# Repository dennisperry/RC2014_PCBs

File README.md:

# PCBs for RC2014
I started with a simple RC2014 Classic II as something interesting to try a new logic analyze. Then built a Zeta2 to get more capability; CP/M etal using ROMWBW. However; the Zeta2 didn't allow for much hardware expansion so I returned to the RC2014 and was confronted with its low cost simplicity. The Classic II is optimized for cost not unfettered expansion. Instead I've redone all the PCBs for the RC2014 with operational independence in mind. No more one clock per system to drive CPU and UART. What I've arrived at is something close to a Zeta2 in RC2014 form factor.

I've used SMT on pretty much all the boards. In my professional life I've done a lot of work with SMT and don't find it that difficult. I'd recommend some solder paste and a hot air setup along with a good soldering iron, a flux pen and various sizes of solder wick. I've converted a toaster oven into a reflow oven for when I'm doing more that one unit builds. This route requires you purchase a solder paste stencil with your PCBs.

No attempt is made to make the boards the same size or particularly pretty, these boards were started with the tariffs at their peak and every sq inch was expensive. The routing is from the FreeRouting plug-in to KiCad. Some of the rough edges are fixed but I didn't want to make them a lifetime project.

If you are a small club or other organization you could get the boards built by someone like JLCPCB or the likes and not have to deal with the SMT issue.

What's missing; generally there is no complete BOM. A BOM can be generated from the KiCad schematic along with looking at the package type. My general practice was to build up a list on Digikey or Mouser as I designed the board. Also combined with what stock I have on hand along with contributions from ebay, Amazon and JameCo.

# 64K RAM/ROM Battery Backed Memory Board for RC2014
One of the last boards I built is a 64k ROM/RAM board without banking. I needed something simpler for a project than the Zeta2 banking system. It is not efficient with memory usage but flexible in being able to make many different memory maps. The ROM can be manually bank selected and will accept any of the SST39SF0x0 flash ICs. The jumpers allow RAM or ROM to traded in 4K block across the memory map. The RAM is battery backed. I use a non-banked version of SCM on this board. If you change your ROM frequently experimenting you will appreciate the 32 pin ZIF socket (look on Amazon for the ZIF).

# Backplane with UART for RC2014

This backplane is built with a 16550 UART which will save 1 slot and pretty much every system will need a basic serial port. The UART is supplied with its own oscillator to make it independent of the other parts of the system.

# Z80 CPU for RC2014
A simple card with its own oscillator which can be either the 8 or 14 pin sizes. Clock can be put on the bus or not by jumper.

# 512K RAM/ROM MEMORY for RC2014
This is a Zeta2 compatible bank select memory board. Allows full ROMWBW CP/M system with ROM and RAM disks. Again experimenters will appreciate the 32 pin ZIF socket. It does lack the battery backup of the Zeta2 so your ROMWBW RAM disk will not survive power cycles.

# 16550 UART for RC2014
Done before the backplane with UART, is Zeta2 compatible using ROMWBW. Has its own clock, and has pinout for a standard FTDI TTL to USB UART adapter.

# Z80 CTC DS1302 RTC for RC2014
This board is Zeta2 compatible with ROMWBW. The RTC is battery backed. Generates periodic interrupts using tpye 2 interrupts.

# PPIDE for RC2014
Again Zeta2 compatible with ROMWBW. Supports power for a CF Card adapter. I use this with a CF card adapter combined with a CF to SD card adapter. You can load all the ROMWBW disk images on a reasonable SD card.

# FDC for RC2014
Zeta2 compatible with ROMWBW. I found that once I had the PPIDE board in my system I really had no need for the FDC but it works fine.

# 8 BIT ARDUINO PRO MICRO INTERFACE for RC2014
Uses the Arduino Pro Micro with a ATmega32U4 with built in USB. WARNING this board has been barely smoke tested. I made it to potentially use it as a UART replacement but have not gotten around to it.

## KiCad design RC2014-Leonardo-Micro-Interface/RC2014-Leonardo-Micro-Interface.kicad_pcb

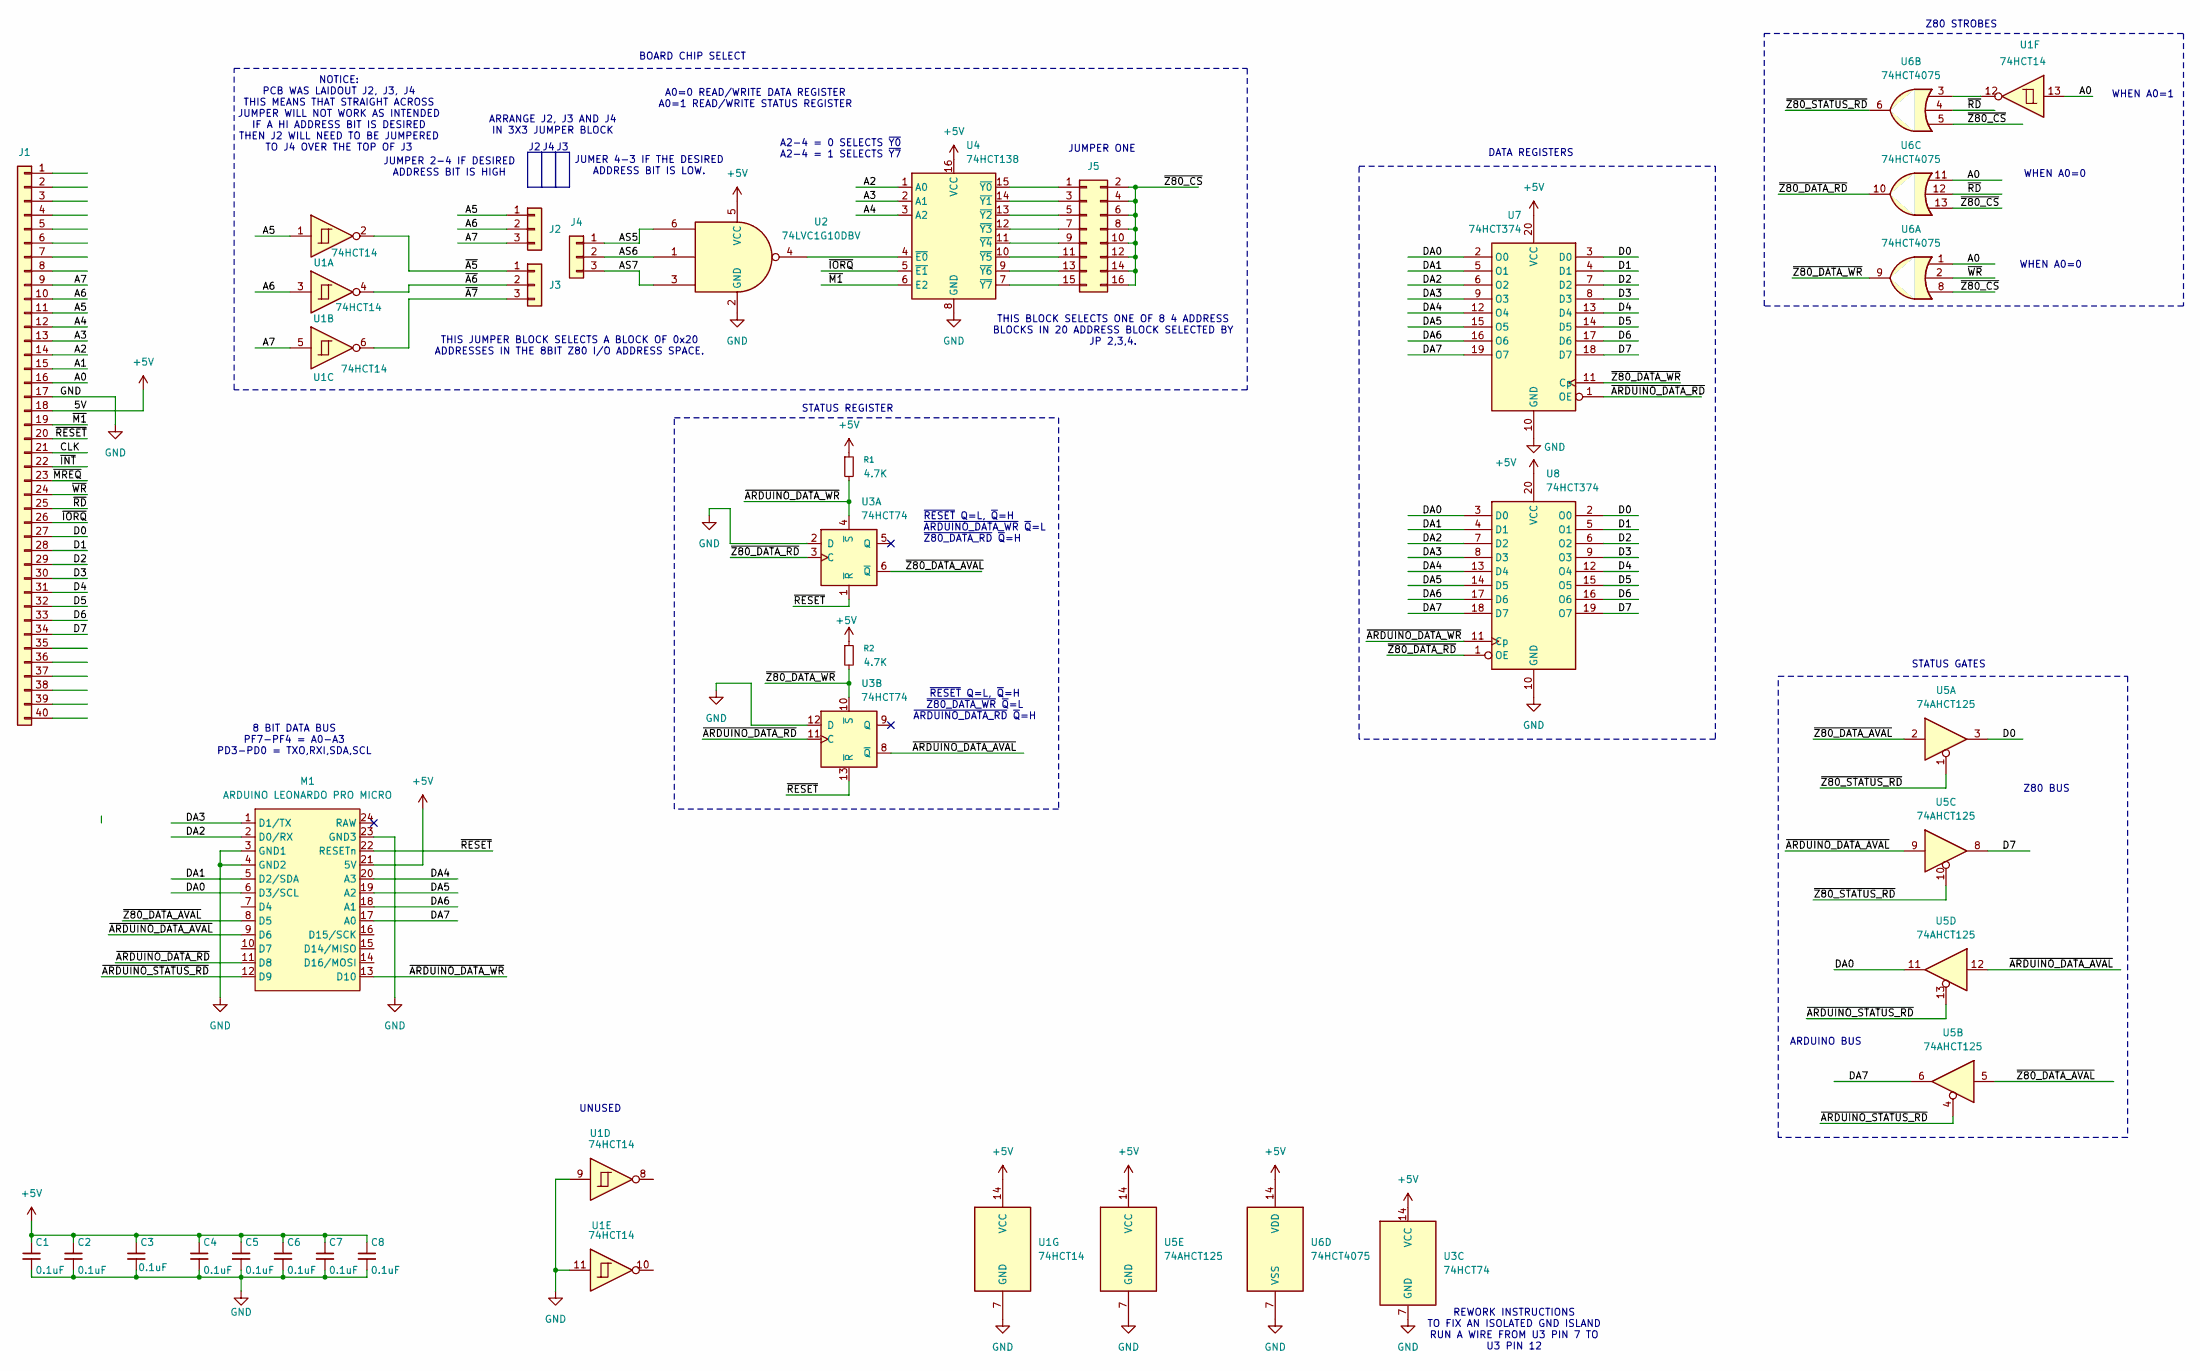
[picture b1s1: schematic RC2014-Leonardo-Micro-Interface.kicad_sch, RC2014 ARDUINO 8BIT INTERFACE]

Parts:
C1, C2, C3, C4, C5, C6, C7, C8: 0.1uF; C_0805_2012Metric_Pad1.18x1.45mm_HandSolder
J1: Conn_01x40; PinHeader_1x40_P2.54mm_Vertical
J2, J3, J4: Conn_01x03; PinHeader_1x03_P2.54mm_Vertical
J5: Conn_02x08_Odd_Even; PinHeader_2x08_P2.54mm_Vertical
M1: ARDUINO LEONARDO PRO MICRO; DIP-24_18.0mmx34.29mm_W15.24mm_Socket
R1, R2: 4.7K; R_0805_2012Metric_Pad1.20x1.40mm_HandSolder
U1: 74HCT14; SO-14_5.3x10.2mm_P1.27mm
U2: 74LVC1G10DBV; SOT-23-6_Handsoldering
U3: 74HCT74; DIP-14_W7.62mm_Socket
U4: 74HCT138; SOIC-16W_5.3x10.2mm_P1.27mm
U5: 74AHCT125; DIP-14_W7.62mm_Socket
U6: 74HCT4075; SO-14_5.3x10.2mm_P1.27mm
U7, U8: 74HCT374; DIP-20_W7.62mm_Socket

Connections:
+5V: C1.1, C2.1, C3.1, C4.1, C5.1, C6.1, C7.1, C8.1, J1.18, M1.21 (5V), R1.1, R2.1, U1.14 (VCC), U2.5 (VCC), U3.14 (VCC), U4.16 (VCC), U5.14 (VCC), U6.14 (VDD), U7.20 (VCC), U8.20 (VCC)
/A0: J1.16, U1.13, U6.1, U6.11
/A1: J1.15
/A2: J1.14, U4.1 (A0)
/A3: J1.13, U4.2 (A1)
/A4: J1.12, U4.3 (A2)
/A5: J1.11, J2.1, U1.1
/A6: J1.10, J2.2, U1.3
/A7: J1.9, J2.3, U1.5
/AS5: J4.1, U2.6
/AS6: J4.2, U2.1
/AS7: J4.3, U2.3
/CLK: J1.21
/D0: J1.27, U5.3, U7.3 (D0), U8.2 (O0)
/D1: J1.28, U7.4 (D1), U8.5 (O1)
/D2: J1.29, U7.7 (D2), U8.6 (O2)
/D3: J1.30, U7.8 (D3), U8.9 (O3)
/D4: J1.31, U7.13 (D4), U8.12 (O4)
/D5: J1.32, U7.14 (D5), U8.15 (O5)
/D6: J1.33, U7.17 (D6), U8.16 (O6)
/D7: J1.34, U5.8, U7.18 (D7), U8.19 (O7)
/DA0: M1.6 (D3/SCL), U5.11, U7.2 (O0), U8.3 (D0)
/DA1: M1.5 (D2/SDA), U7.5 (O1), U8.4 (D1)
/DA2: M1.2 (D0/RX), U7.6 (O2), U8.7 (D2)
/DA3: M1.1 (D1/TX), U7.9 (O3), U8.8 (D3)
/DA4: M1.20 (A3), U7.12 (O4), U8.13 (D4)
/DA5: M1.19 (A2), U7.15 (O5), U8.14 (D5)
/DA6: M1.18 (A1), U7.16 (O6), U8.17 (D6)
/DA7: M1.17 (A0), U5.6, U7.19 (O7), U8.18 (D7)
/~A5: J3.1, U1.2
/~A6: J3.2, U1.4
/~A7: J3.3, U1.6
/~ARDUINO_DATA_AVAL: M1.9 (D6), U3.8 (~Q), U5.9, U5.12
/~ARDUINO_DATA_RD: M1.11 (D8), U3.11 (C), U7.1 (OE)
/~ARDUINO_DATA_WR: M1.13 (D10), R1.2, U3.4 (~S), U8.11 (Cp)
/~ARDUINO_STATUS_RD: M1.12 (D9), U5.4, U5.13
/~INT: J1.22
/~IORQ: J1.26, U4.5 (~E1)
/~M1: J1.19, U4.6 (E2)
/~MREQ: J1.23
/~RD: J1.25, U6.4, U6.12
/~RESET: J1.20, M1.22 (RESETn), U3.1 (~R), U3.13 (~R)
/~WR: J1.24, U6.2
/~Z80_CS: J5.2, J5.4, J5.6, J5.8, J5.10, J5.12, J5.14, J5.16, U6.5, U6.8, U6.13
/~Z80_DATA_AVAL: M1.8 (D5), U3.6 (~Q), U5.2, U5.5
/~Z80_DATA_RD: U3.3 (C), U6.10, U8.1 (OE)
/~Z80_DATA_WR: R2.2, U3.10 (~S), U6.9, U7.11 (Cp)
/~Z80_STATUS_RD: U5.1, U5.10, U6.6
GND: C1.2, C2.2, C3.2, C4.2, C5.2, C6.2, C7.2, C8.2, J1.17, M1.3 (GND1), M1.4 (GND2), M1.23 (GND3), U1.7 (GND), U1.9, U1.11, U2.2 (GND), U3.2 (D), U3.7 (GND), U3.12 (D), U4.8 (GND), U5.7 (GND), U6.7 (VSS), U7.10 (GND), U8.10 (GND)
unnamed: J5.1, U4.15 (~Y0)
unnamed: J5.3, U4.14 (~Y1)
unnamed: J5.5, U4.13 (~Y2)
unnamed: J5.7, U4.12 (~Y3)
unnamed: J5.9, U4.11 (~Y4)
unnamed: J5.11, U4.10 (~Y5)
unnamed: J5.13, U4.9 (~Y6)
unnamed: J5.15, U4.7 (~Y7)
unnamed: U1.12, U6.3
unnamed: U2.4, U4.4 (~E0)

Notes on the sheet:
STATUS REGISTER
THIS JUMPER BLOCK SELECTS A BLOCK OF 0x20 ADDRESSES IN THE 8BIT Z80 I/O ADDRESS SPACE.
8 BIT DATA BUS PF7-PF4 = A0-A3 PD3-PD0 = TXO,RXI,SDA,SCL
ARRANGE J2, J3 AND J4 IN 3X3 JUMPER BLOCK
DATA REGISTERS
A0=0 READ/WRITE DATA REGISTER A0=1 READ/WRITE STATUS REGISTER
STATUS GATES
JUMPER ONE
BOARD CHIP SELECT
~{RESET} Q=L, ~{Q}=H ~{ARDUINO_DATA_WR} ~{Q}=L ~{Z80_DATA_RD} ~{Q}=H
WHEN A0=0
A2-4 = 0 SELECTS ~{Y0} A2-4 = 1 SELECTS ~{Y7}
REWORK INSTRUCTIONS TO FIX AN ISOLATED GND ISLAND RUN A WIRE FROM U3 PIN 7 TO U3 PIN 12
ARDUINO BUS
~{RESET} Q=L, ~{Q}=H ~{Z80_DATA_WR} ~{Q}=L ~{ARDUINO_DATA_RD} ~{Q}=H
JUMER 4-3 IF THE DESIRED ADDRESS BIT IS LOW.
Z80 BUS
WHEN A0=1
UNUSED
Z80 STROBES
THIS BLOCK SELECTS ONE OF 8 4 ADDRESS BLOCKS IN 20 ADDRESS BLOCK SELECTED BY JP 2,3,4.
NOTICE: PCB WAS LAIDOUT J2, J3, J4 THIS MEANS THAT STRAIGHT ACROSS JUMPER WILL NOT WORK AS INTENDED IF A HI ADDRESS BIT IS DESIRED THEN J2 WILL NEED TO BE JUMPERED TO J4 OVER THE TOP OF J3
JUMPER 2-4 IF DESIRED ADDRESS BIT IS HIGH

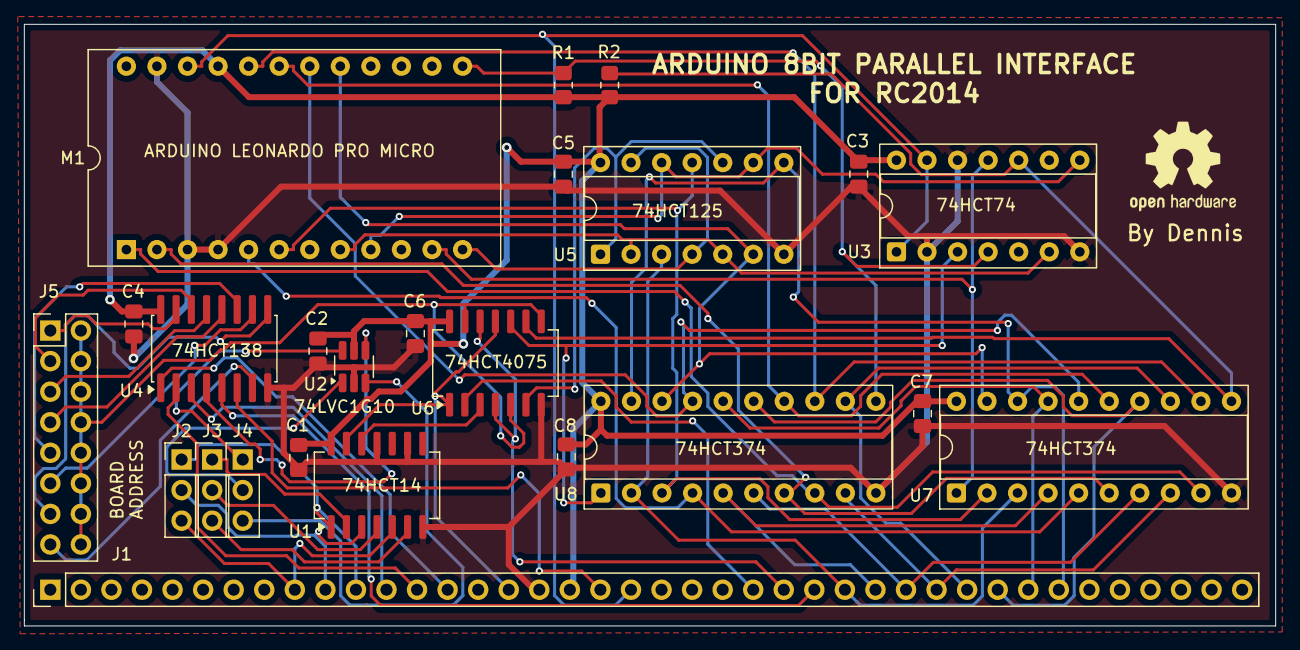
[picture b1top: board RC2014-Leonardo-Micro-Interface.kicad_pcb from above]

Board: 2 copper layers, 104.0 x 50.0 mm, 24 parts (0 on the bottom side), 55 nets.

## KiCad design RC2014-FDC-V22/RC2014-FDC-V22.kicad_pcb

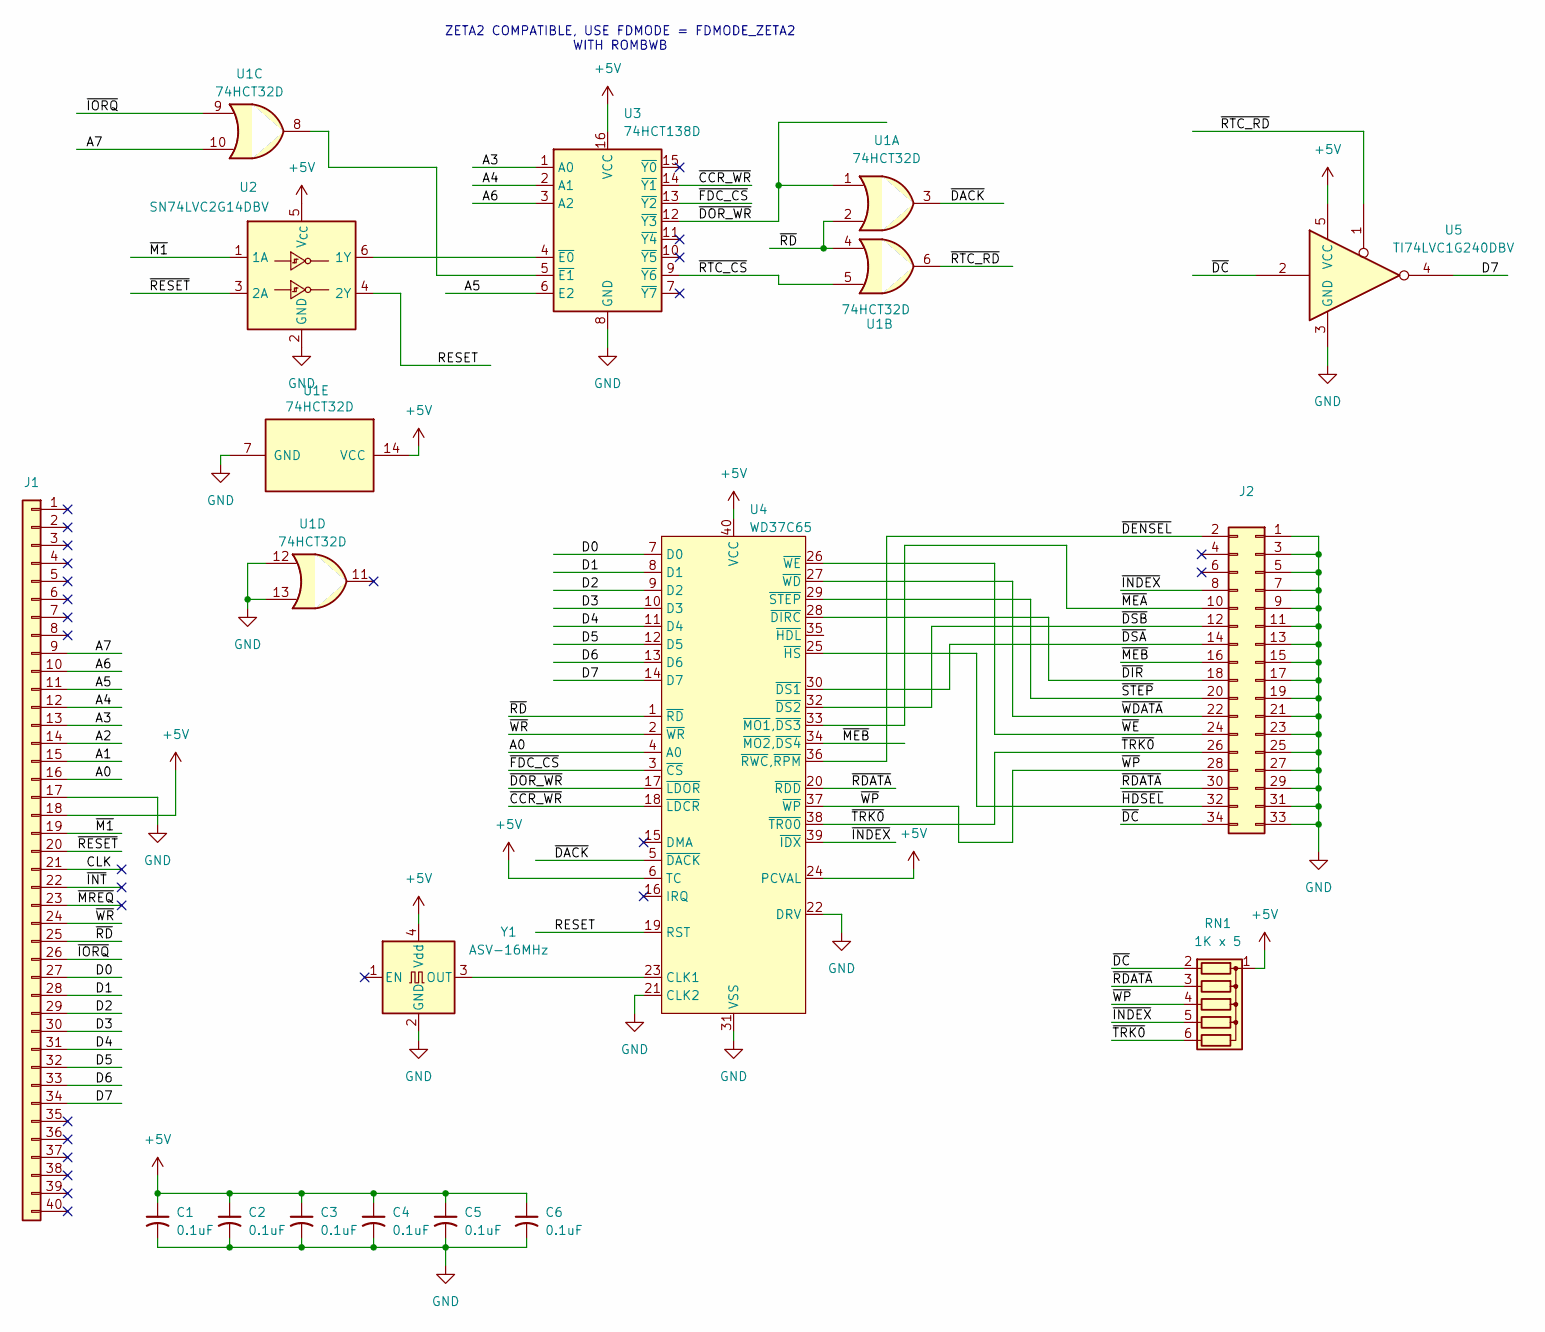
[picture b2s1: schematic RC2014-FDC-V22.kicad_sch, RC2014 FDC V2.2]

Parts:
C1, C2, C3, C4, C5, C6: 0.1uF; C_0805_2012Metric_Pad1.18x1.45mm_HandSolder
J1: Conn_01x40; PinHeader_1x40_P2.54mm_Vertical
J2: Conn_02x17_Odd_Even; PinHeader_2x17_P2.54mm_Vertical
RN1: 1K x 5; R_Array_SIP6
U1: 74HCT32D; SO-14_5.3x10.2mm_P1.27mm
U2: SN74LVC2G14DBV; SOT-23-6_Handsoldering
U3: 74HCT138D; SOIC-16_4.55x10.3mm_P1.27mm
U4: WD37C65; DIP-40_W15.24mm_Socket
U5: TI74LVC1G240DBV; SOT-23-5_HandSoldering
Y1: ASV-16MHz; Oscillator_SMD_Abracon_ASV-4Pin_7.0x5.1mm

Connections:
+5V: C1.1, C2.1, C3.1, C4.1, C5.1, C6.1, J1.18, RN1.1 (common), U1.14 (VCC), U2.5 (V_{CC}), U3.16 (VCC), U4.6 (TC), U4.24 (PCVAL), U4.40 (VCC), U5.5 (VCC), Y1.4 (Vdd)
/A0: J1.16, U4.4 (A0)
/A1: J1.15
/A2: J1.14
/A3: J1.13, U3.1 (A0)
/A4: J1.12, U3.2 (A1)
/A5: J1.11, U3.6 (E2)
/A6: J1.10, U3.3 (A2)
/A7: J1.9, U1.10
/CLK: J1.21
/D0: J1.27, U4.7 (D0)
/D1: J1.28, U4.8 (D1)
/D2: J1.29, U4.9 (D2)
/D3: J1.30, U4.10 (D3)
/D4: J1.31, U4.11 (D4)
/D5: J1.32, U4.12 (D5)
/D6: J1.33, U4.13 (D6)
/D7: J1.34, U4.14 (D7), U5.4
/RESET: U2.4 (2Y), U4.19 (RST)
/~CCR_WR: U3.14 (~Y1), U4.18 (~LDCR)
/~DACK: U1.3, U4.5 (~DACK)
/~DC: J2.34, RN1.2 (R1), U5.2
/~DENSEL: J2.2, U4.36 (~RWC,~RPM)
/~DIR: J2.18, U4.28 (~DIRC)
/~DOR_WR: U1.1, U3.12 (~Y3), U4.17 (~LDOR)
/~DSA: J2.14, U4.30 (~DS1)
/~DSB: J2.12, U4.32 (~DS2)
/~FDC_CS: U3.13 (~Y2), U4.3 (~CS)
/~HDSEL: J2.32, U4.25 (~HS)
/~INDEX: J2.8, RN1.5 (R4), U4.39 (~IDX)
/~INT: J1.22
/~IORQ: J1.26, U1.9
/~M1: J1.19, U2.1 (1A)
/~MEA: J2.10, U4.33 (~MO1,~DS3)
/~MEB: J2.16, U4.34 (~MO2,~DS4)
/~MREQ: J1.23
/~RDATA: J2.30, RN1.3 (R2), U4.20 (~RDD)
/~RD: J1.25, U1.2, U1.4, U4.1 (~RD)
/~RESET: J1.20, U2.3 (2A)
/~RTC_CS: U1.5, U3.9 (~Y6)
/~RTC_RD: U1.6, U5.1
/~STEP: J2.20, U4.29 (~STEP)
/~TRK0: J2.26, RN1.6 (R5), U4.38 (~TR00)
/~WDATA: J2.22, U4.27 (~WD)
/~WE: J2.24, U4.26 (~WE)
/~WP: J2.28, RN1.4 (R3), U4.37 (~WP)
/~WR: J1.24, U4.2 (~WR)
GND: C1.2, C2.2, C3.2, C4.2, C5.2, C6.2, J1.17, J2.1, J2.3, J2.5, J2.7, J2.9, J2.11, J2.13, J2.15, J2.17, J2.19, J2.21, J2.23, J2.25, J2.27, J2.29, J2.31, J2.33, U1.7 (GND), U1.12, U1.13, U2.2 (GND), U3.8 (GND), U4.21 (CLK2), U4.22 (DRV), U4.31 (VSS), U5.3 (GND), Y1.2 (GND)
unnamed: U2.6 (1Y), U3.4 (~E0)
unnamed: U1.8, U3.5 (~E1)
unnamed: U4.23 (CLK1), Y1.3 (OUT)

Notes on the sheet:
ZETA2 COMPATIBLE, USE FDMODE = FDMODE_ZETA2 WITH ROMBWB

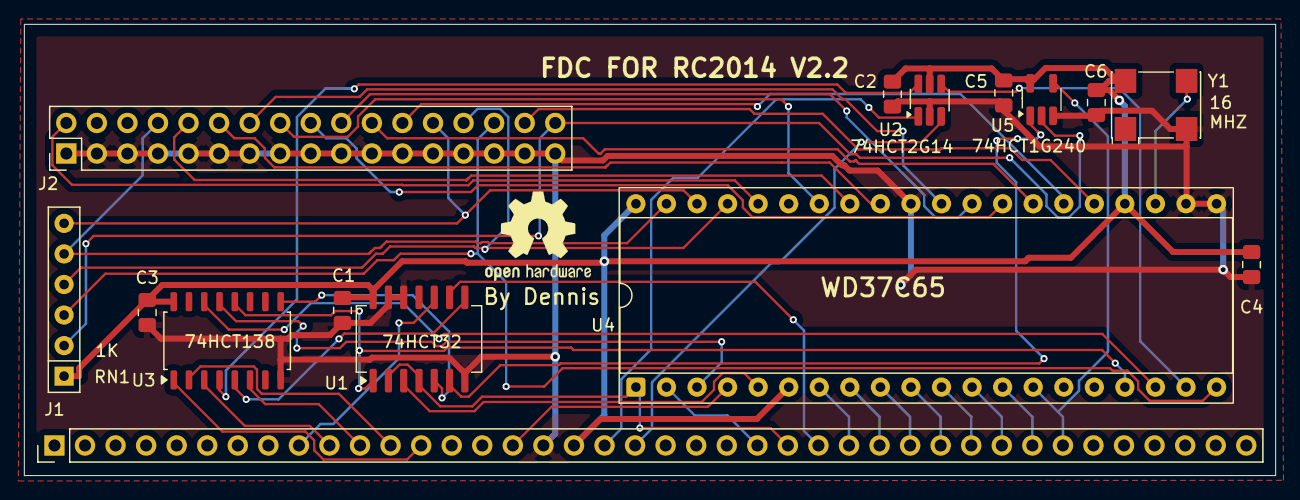
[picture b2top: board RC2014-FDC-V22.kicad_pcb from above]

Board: 2 copper layers, 104.0 x 37.5 mm, 15 parts (0 on the bottom side), 46 nets.

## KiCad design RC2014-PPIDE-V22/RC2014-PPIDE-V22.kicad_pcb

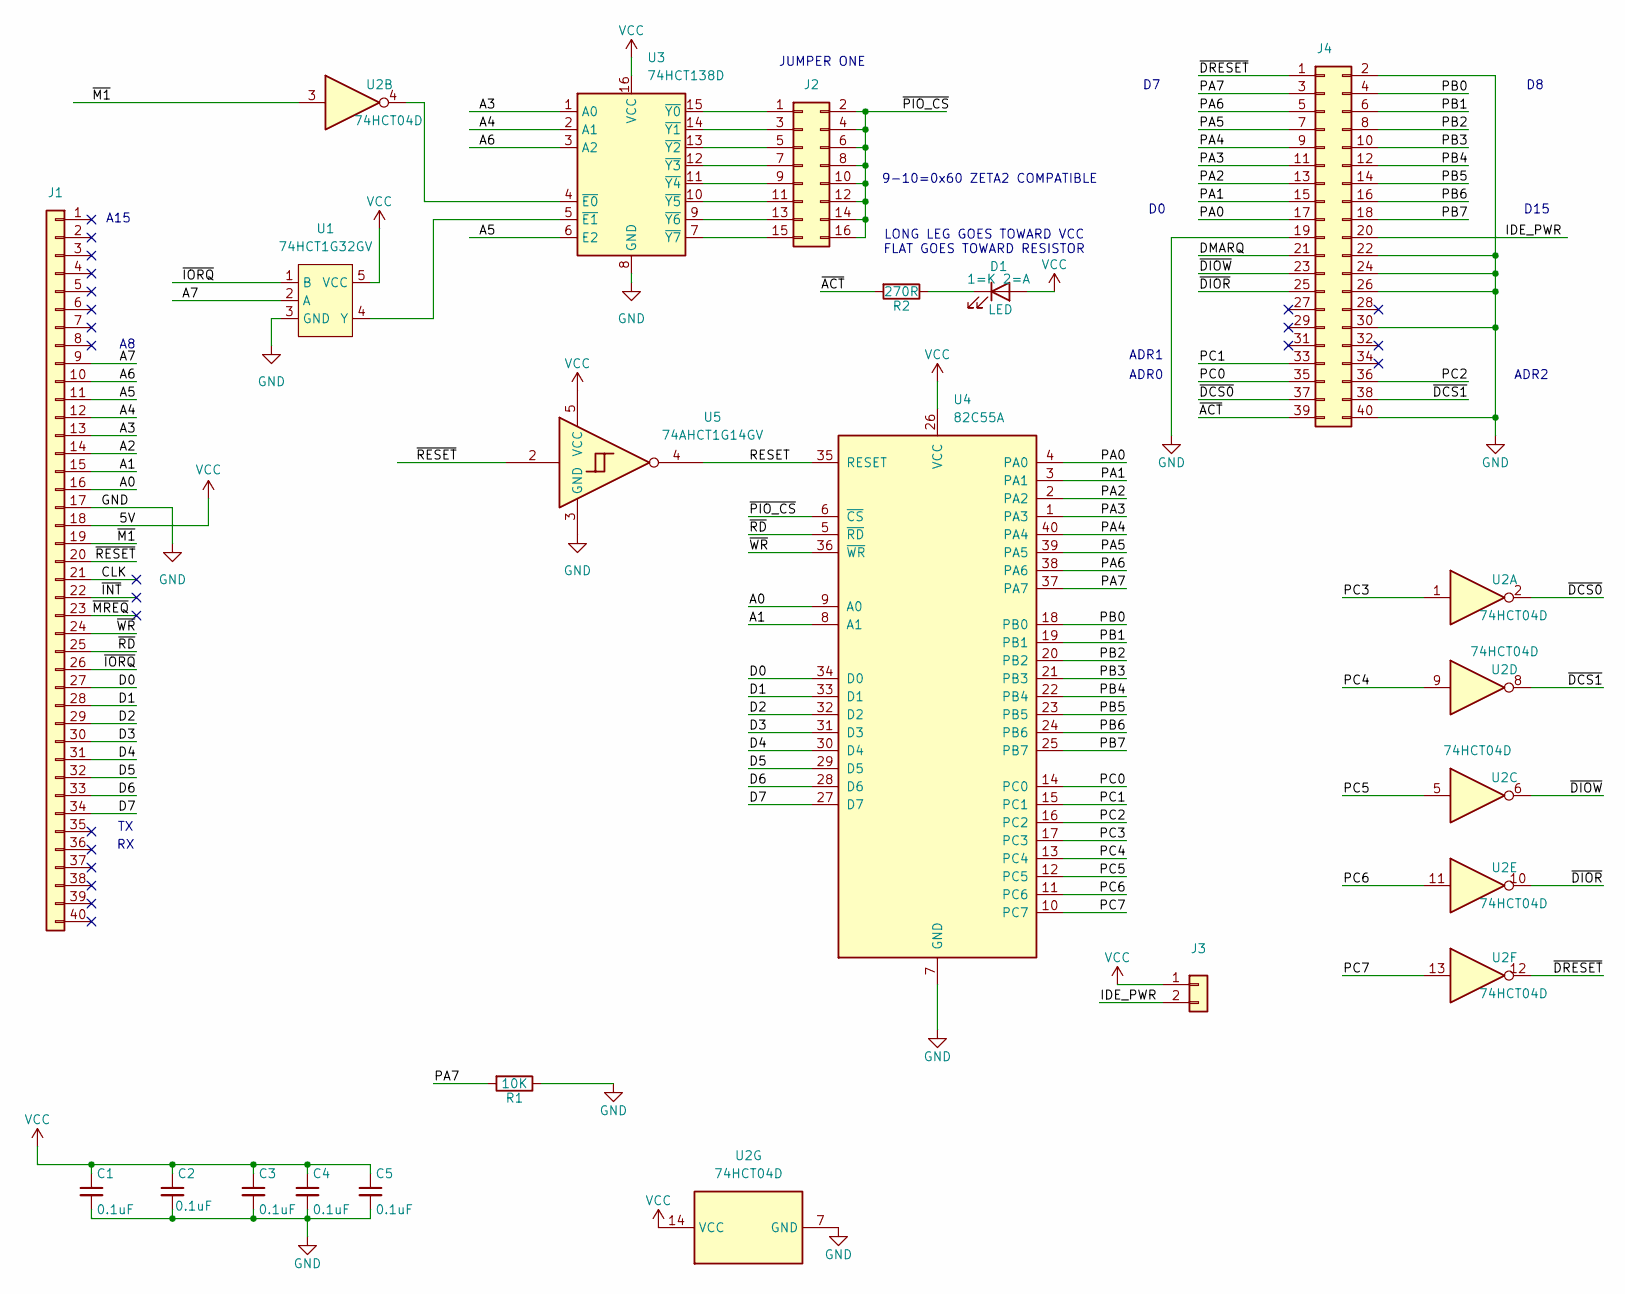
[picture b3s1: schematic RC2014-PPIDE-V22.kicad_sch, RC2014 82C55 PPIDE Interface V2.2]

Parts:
C1, C2, C3, C4, C5: 0.1uF; C_0805_2012Metric_Pad1.18x1.45mm_HandSolder
D1: LED; LED_D3.0mm
J1: Conn_01x40; PinHeader_1x40_P2.54mm_Vertical
J2: Conn_02x08_Odd_Even; PinHeader_2x08_P2.54mm_Vertical
J3: Conn_01x02; PinHeader_1x02_P2.54mm_Vertical
J4: Conn_02x20_Odd_Even; PinHeader_2x20_P2.54mm_Vertical
R1: 10K; R_0805_2012Metric_Pad1.20x1.40mm_HandSolder
R2: 270R; R_0805_2012Metric_Pad1.20x1.40mm_HandSolder
U1: 74HCT1G32GV; SC-74A-5_1.55x2.9mm_P0.95mm
U2: 74HCT04D; SOIC-14_3.9x8.7mm_P1.27mm
U3: 74HCT138D; SOIC-16W_5.3x10.2mm_P1.27mm
U4: 82C55A; DIP-40_W15.24mm
U5: 74AHCT1G14GV; SC-74A-5_1.55x2.9mm_P0.95mm

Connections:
/A0: J1.16, U4.9 (A0)
/A1: J1.15, U4.8 (A1)
/A2: J1.14
/A3: J1.13, U3.1 (A0)
/A4: J1.12, U3.2 (A1)
/A5: J1.11, U3.6 (E2)
/A6: J1.10, U3.3 (A2)
/A7: J1.9, U1.2 (A)
/CLK: J1.21
/D0: J1.27, U4.34 (D0)
/D1: J1.28, U4.33 (D1)
/D2: J1.29, U4.32 (D2)
/D3: J1.30, U4.31 (D3)
/D4: J1.31, U4.30 (D4)
/D5: J1.32, U4.29 (D5)
/D6: J1.33, U4.28 (D6)
/D7: J1.34, U4.27 (D7)
/DMARQ: J4.21
/IDE_PWR: J3.2, J4.20
/PA0: J4.17, U4.4 (PA0)
/PA1: J4.15, U4.3 (PA1)
/PA2: J4.13, U4.2 (PA2)
/PA3: J4.11, U4.1 (PA3)
/PA4: J4.9, U4.40 (PA4)
/PA5: J4.7, U4.39 (PA5)
/PA6: J4.5, U4.38 (PA6)
/PA7: J4.3, R1.2, U4.37 (PA7)
/PB0: J4.4, U4.18 (PB0)
/PB1: J4.6, U4.19 (PB1)
/PB2: J4.8, U4.20 (PB2)
/PB3: J4.10, U4.21 (PB3)
/PB4: J4.12, U4.22 (PB4)
/PB5: J4.14, U4.23 (PB5)
/PB6: J4.16, U4.24 (PB6)
/PB7: J4.18, U4.25 (PB7)
/PC0: J4.35, U4.14 (PC0)
/PC1: J4.33, U4.15 (PC1)
/PC2: J4.36, U4.16 (PC2)
/PC3: U2.1, U4.17 (PC3)
/PC4: U2.9, U4.13 (PC4)
/PC5: U2.5, U4.12 (PC5)
/PC6: U2.11, U4.11 (PC6)
/PC7: U2.13, U4.10 (PC7)
/RESET: U4.35 (RESET), U5.4
/~ACT: J4.39, R2.2
/~DCS0: J4.37, U2.2
/~DCS1: J4.38, U2.8
/~DIOR: J4.25, U2.10
/~DIOW: J4.23, U2.6
/~DRESET: J4.1, U2.12
/~INT: J1.22
/~IORQ: J1.26, U1.1 (B)
/~M1: J1.19, U2.3
/~MREQ: J1.23
/~PIO_CS: J2.2, J2.4, J2.6, J2.8, J2.10, J2.12, J2.14, J2.16, U4.6 (~CS)
/~RD: J1.25, U4.5 (~RD)
/~RESET: J1.20, U5.2
/~WR: J1.24, U4.36 (~WR)
GND: C1.2, C2.2, C3.2, C4.2, C5.2, J1.17, J4.2, J4.19, J4.22, J4.24, J4.26, J4.30, J4.40, R1.1, U1.3 (GND), U2.7 (GND), U3.8 (GND), U4.7 (GND), U5.3 (GND)
unnamed: D1.1 (K), R2.1
unnamed: J2.1, U3.15 (~Y0)
unnamed: J2.3, U3.14 (~Y1)
unnamed: J2.5, U3.13 (~Y2)
unnamed: J2.7, U3.12 (~Y3)
unnamed: J2.9, U3.11 (~Y4)
unnamed: J2.11, U3.10 (~Y5)
unnamed: J2.13, U3.9 (~Y6)
unnamed: J2.15, U3.7 (~Y7)
unnamed: U1.4 (Y), U3.5 (~E1)
unnamed: U2.4, U3.4 (~E0)
VCC: C1.1, C2.1, C3.1, C4.1, C5.1, D1.2 (A), J1.18, J3.1, U1.5 (VCC), U2.14 (VCC), U3.16 (VCC), U4.26 (VCC), U5.5 (VCC)

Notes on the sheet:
LONG LEG GOES TOWARD VCC FLAT GOES TOWARD RESISTOR
9-10=0x60 ZETA2 COMPATIBLE
JUMPER ONE
D15
ADR0
ADR1
ADR2
A15

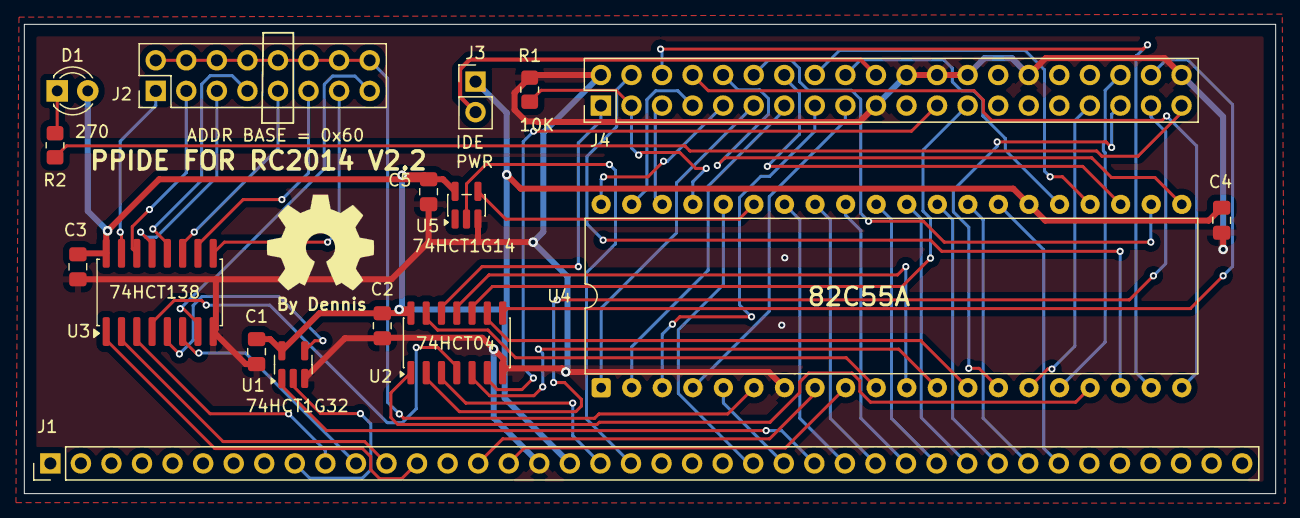
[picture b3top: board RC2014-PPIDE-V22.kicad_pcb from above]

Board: 2 copper layers, 104.0 x 39.0 mm, 17 parts (0 on the bottom side), 66 nets.

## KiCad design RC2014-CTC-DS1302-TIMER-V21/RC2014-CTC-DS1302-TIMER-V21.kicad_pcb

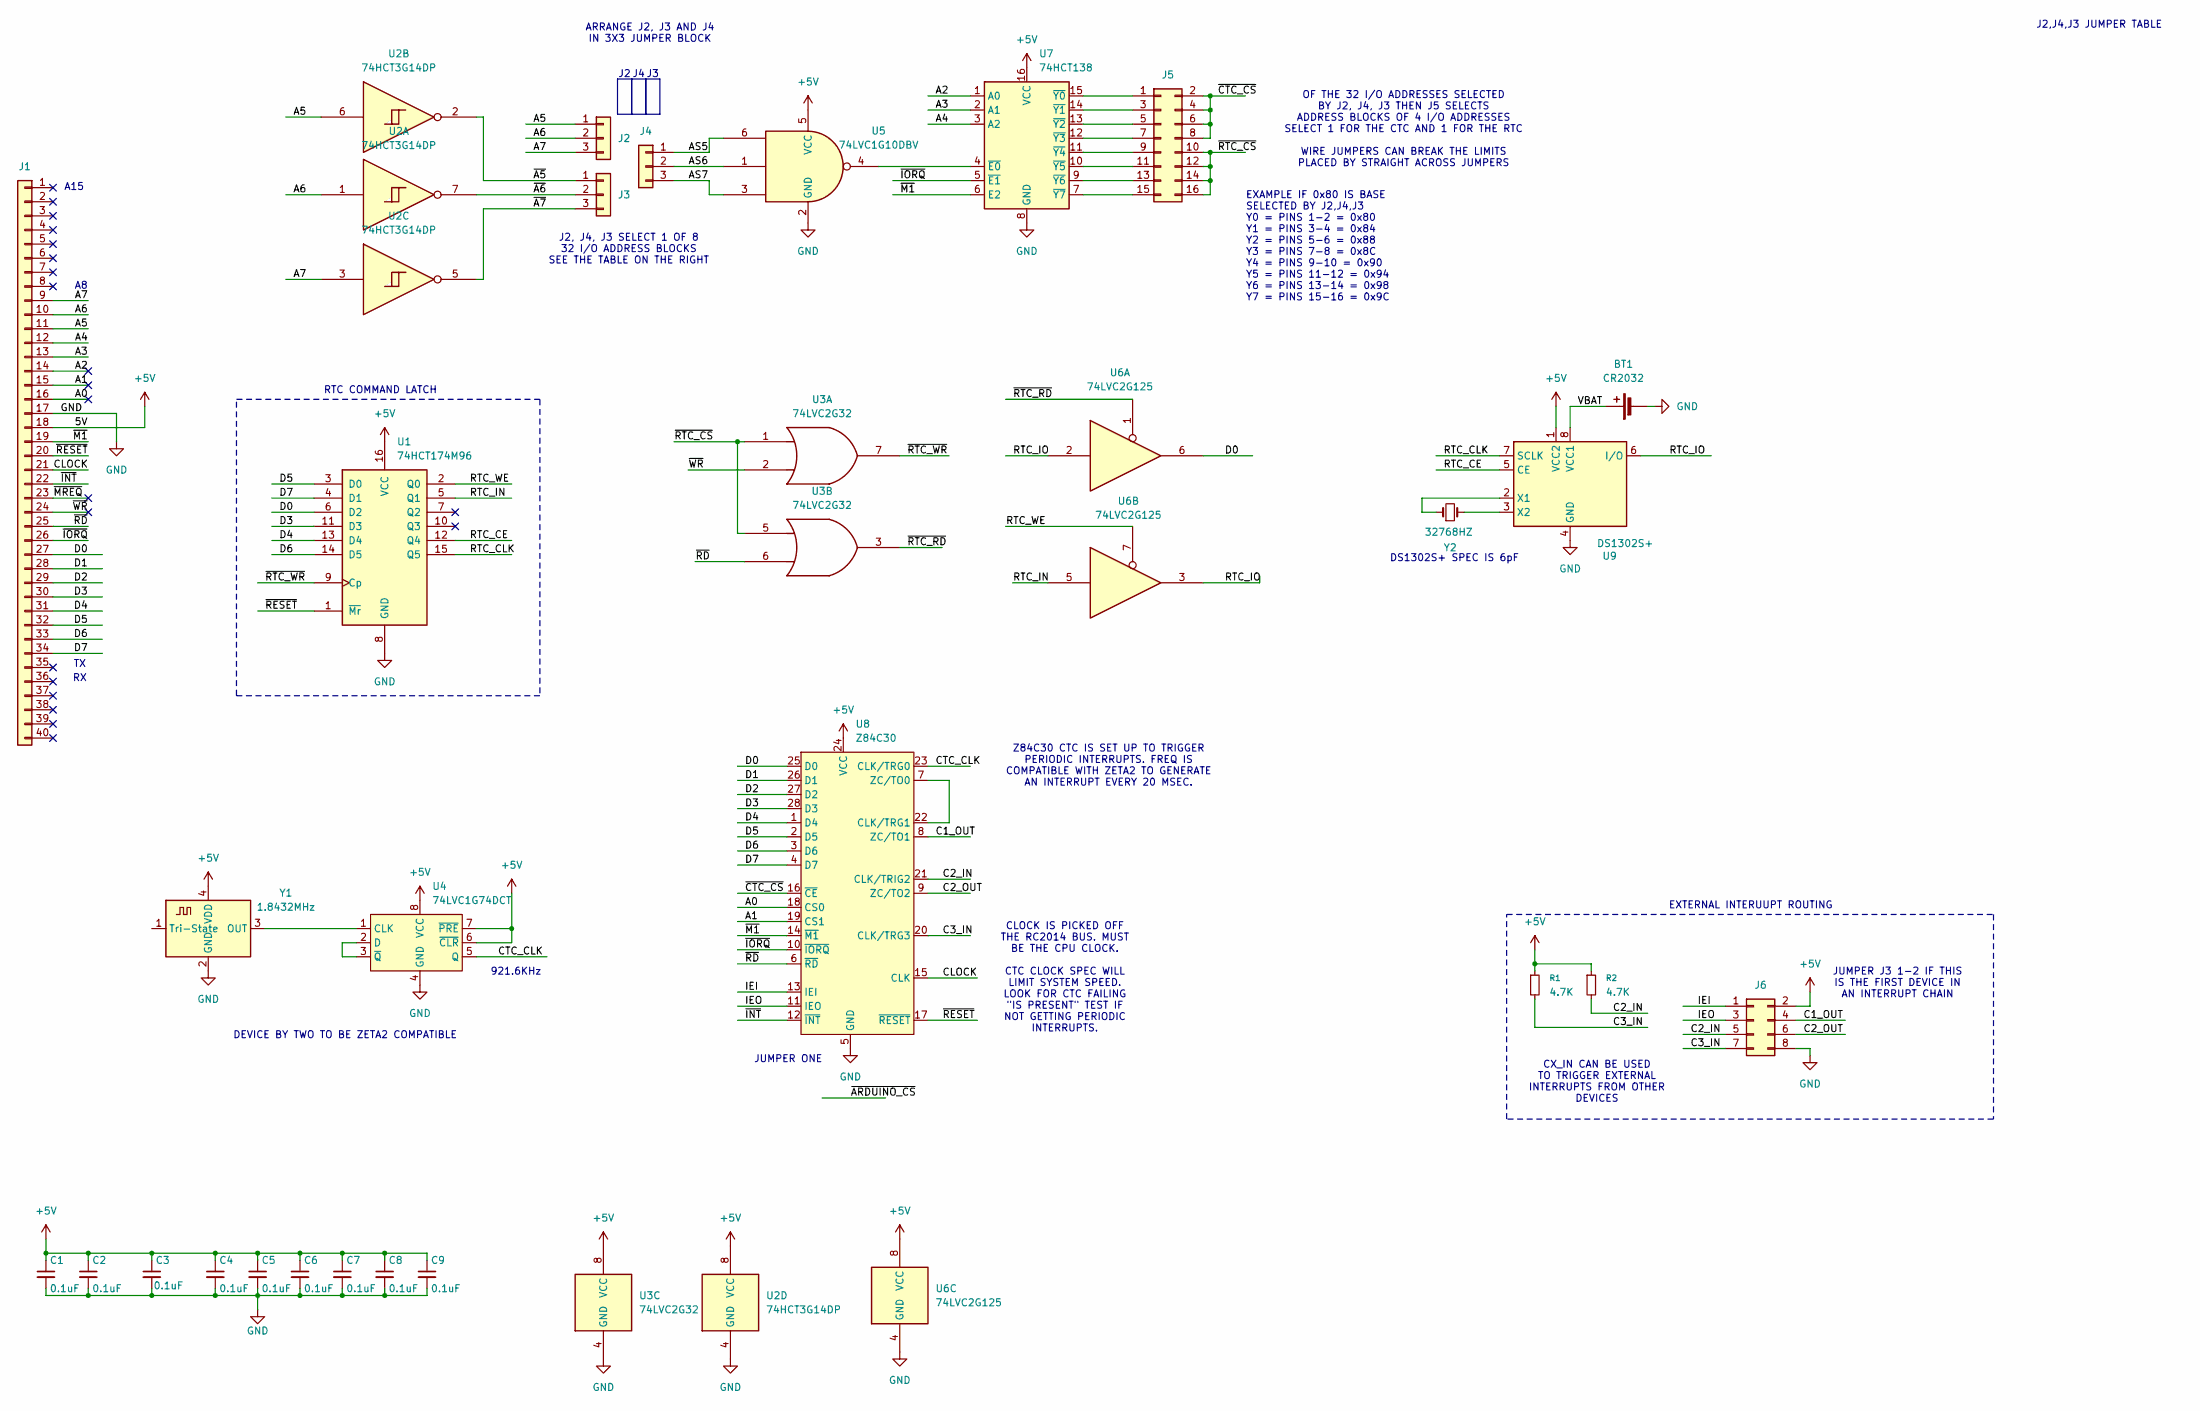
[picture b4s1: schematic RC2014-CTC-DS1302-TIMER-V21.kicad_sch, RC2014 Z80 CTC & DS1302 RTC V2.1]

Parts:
BT1: CR2032; 2032BAT-HOLDER
C1, C2, C3, C4, C5, C6, C7, C8, C9: 0.1uF; C_0805_2012Metric_Pad1.18x1.45mm_HandSolder
J1: Conn_01x40; PinHeader_1x40_P2.54mm_Vertical
J2, J3, J4: Conn_01x03; PinHeader_1x03_P2.54mm_Vertical
J5: Conn_02x08_Odd_Even; PinHeader_2x08_P2.54mm_Vertical
J6: PinHeader_2x04_P2.54mm_Vertical
R1, R2: 4.7K; R_0805_2012Metric_Pad1.20x1.40mm_HandSolder
U1: 74HCT174M96; SOIC-16_4.55x10.3mm_P1.27mm
U2: 74HCT3G14DP; TSSOP-8_3x3mm_P0.65mm
U3: 74LVC2G32; TSSOP-8_3x3mm_P0.65mm
U4: 74LVC1G74DCT; SSOP-8_2.95x2.8mm_P0.65mm
U5: 74LVC1G10DBV; SOT-23-6_Handsoldering
U6: 74LVC2G125; SSOP-8_2.95x2.8mm_P0.65mm
U7: 74HCT138; SOIC-16_4.55x10.3mm_P1.27mm
U8: Z84C30; DIP-28_W15.24mm
U9: DS1302S+; SOIC-8_5.3x5.3mm_P1.27mm
Y1: 1.8432MHz; Oscillator_SMD_EuroQuartz_XO91-4Pin_7.0x5.0mm_HandSoldering
Y2: 32768HZ; Crystal_C26-LF_D2.1mm_L6.5mm_Horizontal

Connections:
+5V: C1.1, C2.1, C3.1, C4.1, C5.1, C6.1, C7.1, C8.1, C9.1, J1.18, J6.2, R1.1, R2.1, U1.16 (VCC), U2.8 (VCC), U3.8 (VCC), U4.6 (~CLR), U4.7 (~PRE), U4.8 (VCC), U5.5 (VCC), U6.8 (VCC), U7.16 (VCC), U8.24 (VCC), U9.1 (VCC2), Y1.4 (VDD)
/A0: J1.16, U8.18 (CS0)
/A1: J1.15, U8.19 (CS1)
/A2: J1.14, U7.1 (A0)
/A3: J1.13, U7.2 (A1)
/A4: J1.12, U7.3 (A2)
/A5: J1.11, J2.1, U2.6
/A6: J1.10, J2.2, U2.1
/A7: J1.9, J2.3, U2.3
/AS5: J4.1, U5.6
/AS6: J4.2, U5.1
/AS7: J4.3, U5.3
/C1_OUT: J6.4, U8.8 (ZC/TO1)
/C2_IN: J6.5, R2.2, U8.21 (CLK/TRIG2)
/C2_OUT: J6.6, U8.9 (ZC/TO2)
/C3_IN: J6.7, R1.2, U8.20 (CLK/TRG3)
/CLOCK: J1.21, U8.15 (CLK)
/CTC_CLK: U4.5 (Q), U8.23 (CLK/TRG0)
/D0: J1.27, U1.6 (D2), U6.6, U8.25 (D0)
/D1: J1.28, U8.26 (D1)
/D2: J1.29, U8.27 (D2)
/D3: J1.30, U1.11 (D3), U8.28 (D3)
/D4: J1.31, U1.13 (D4), U8.1 (D4)
/D5: J1.32, U1.3 (D0), U8.2 (D5)
/D6: J1.33, U1.14 (D5), U8.3 (D6)
/D7: J1.34, U1.4 (D1), U8.4 (D7)
/IEI: J6.1, U8.13 (IEI)
/IEO: J6.3, U8.11 (IEO)
/RTC_CE: U1.12 (Q4), U9.5 (CE)
/RTC_CLK: U1.15 (Q5), U9.7 (SCLK)
/RTC_IN: U1.5 (Q1), U6.5
/RTC_IO: U6.2, U6.3, U9.6 (I/O)
/RTC_WE: U1.2 (Q0), U6.7
/VBAT: BT1.1 (+), U9.8 (VCC1)
/~A5: J3.1, U2.2
/~A6: J3.2, U2.7
/~A7: J3.3, U2.5
/~CTC_CS: J5.2, J5.4, J5.6, J5.8, U8.16 (~CE)
/~INT: J1.22, U8.12 (~INT)
/~IORQ: J1.26, U7.5 (~E1), U8.10 (~IORQ)
/~M1: J1.19, U7.6 (E2), U8.14 (~M1)
/~MREQ: J1.23
/~RD: J1.25, U3.6, U8.6 (~RD)
/~RESET: J1.20, U1.1 (~Mr), U8.17 (~RESET)
/~RTC_CS: J5.10, J5.12, J5.14, J5.16, U3.1, U3.5
/~RTC_RD: U3.3, U6.1
/~RTC_WR: U1.9 (Cp), U3.7
/~WR: J1.24, U3.2
GND: BT1.2 (-), C1.2, C2.2, C3.2, C4.2, C5.2, C6.2, C7.2, C8.2, C9.2, J1.17, J6.8, U1.8 (GND), U2.4 (GND), U3.4 (GND), U4.4 (GND), U5.2 (GND), U6.4 (GND), U7.8 (GND), U8.5 (GND), U9.4 (GND), Y1.2 (GND)
unnamed: J5.1, U7.15 (~Y0)
unnamed: J5.3, U7.14 (~Y1)
unnamed: J5.5, U7.13 (~Y2)
unnamed: J5.7, U7.12 (~Y3)
unnamed: J5.9, U7.11 (~Y4)
unnamed: J5.11, U7.10 (~Y5)
unnamed: J5.13, U7.9 (~Y6)
unnamed: J5.15, U7.7 (~Y7)
unnamed: U4.1 (CLK), Y1.3 (OUT)
unnamed: U4.2 (D), U4.3 (~Q)
unnamed: U5.4, U7.4 (~E0)
unnamed: U8.7 (ZC/TO0), U8.22 (CLK/TRG1)
unnamed: U9.2 (X1), Y2.1
unnamed: U9.3 (X2), Y2.2

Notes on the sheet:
J2, J4, J3 SELECT 1 OF 8 32 I/O ADDRESS BLOCKS SEE THE TABLE ON THE RIGHT
JUMPER ONE
JUMPER J3 1-2 IF THIS IS THE FIRST DEVICE IN AN INTERRUPT CHAIN
ARRANGE J2, J3 AND J4 IN 3X3 JUMPER BLOCK
OF THE 32 I/O ADDRESSES SELECTED BY J2, J4, J3 THEN J5 SELECTS ADDRESS BLOCKS OF 4 I/O ADDRESSES SELECT 1 FOR THE CTC AND 1 FOR THE RTC WIRE JUMPERS CAN BREAK THE LIMITS PLACED BY STRAIGHT ACROSS JUMPERS
DEVICE BY TWO TO BE ZETA2 COMPATIBLE
EXAMPLE IF 0x80 IS BASE SELECTED BY J2,J4,J3 Y0 = PINS 1-2 = 0x80 Y1 = PINS 3-4 = 0x84 Y2 = PINS 5-6 = 0x88 Y3 = PINS 7-8 = 0x8C Y4 = PINS 9-10 = 0x90 Y5 = PINS 11-12 = 0x94 Y6 = PINS 13-14 = 0x98 Y7 = PINS 15-16 = 0x9C
921.6KHz
EXTERNAL INTERUUPT ROUTING
CLOCK IS PICKED OFF THE RC2014 BUS. MUST BE THE CPU CLOCK. CTC CLOCK SPEC WILL LIMIT SYSTEM SPEED. LOOK FOR CTC FAILING "IS PRESENT" TEST IF NOT GETTING PERIODIC INTERRUPTS.
RTC COMMAND LATCH
J2,J4,J3 JUMPER TABLE
Z84C30 CTC IS SET UP TO TRIGGER PERIODIC INTERRUPTS. FREQ IS COMPATIBLE WITH ZETA2 TO GENERATE AN INTERRUPT EVERY 20 MSEC.
CX_IN CAN BE USED TO TRIGGER EXTERNAL INTERRUPTS FROM OTHER DEVICES
DS1302S+ SPEC IS 6pF
A15

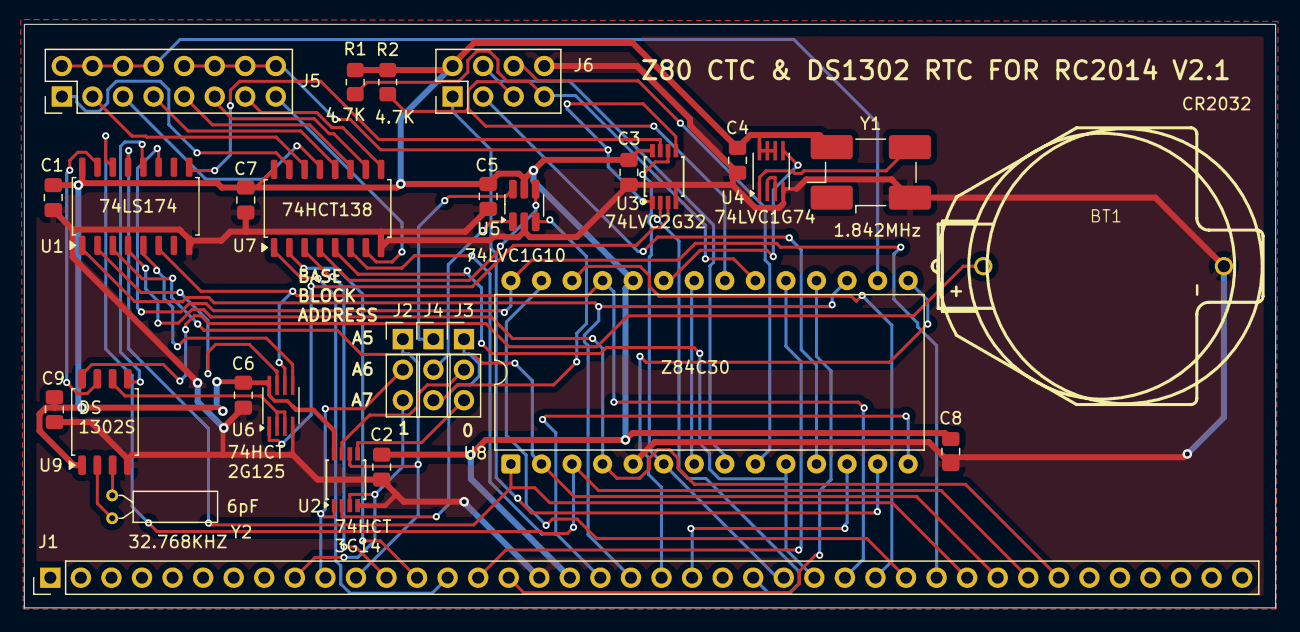
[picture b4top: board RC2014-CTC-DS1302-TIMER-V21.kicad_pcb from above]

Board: 2 copper layers, 104.0 x 48.5 mm, 29 parts (0 on the bottom side), 62 nets.
